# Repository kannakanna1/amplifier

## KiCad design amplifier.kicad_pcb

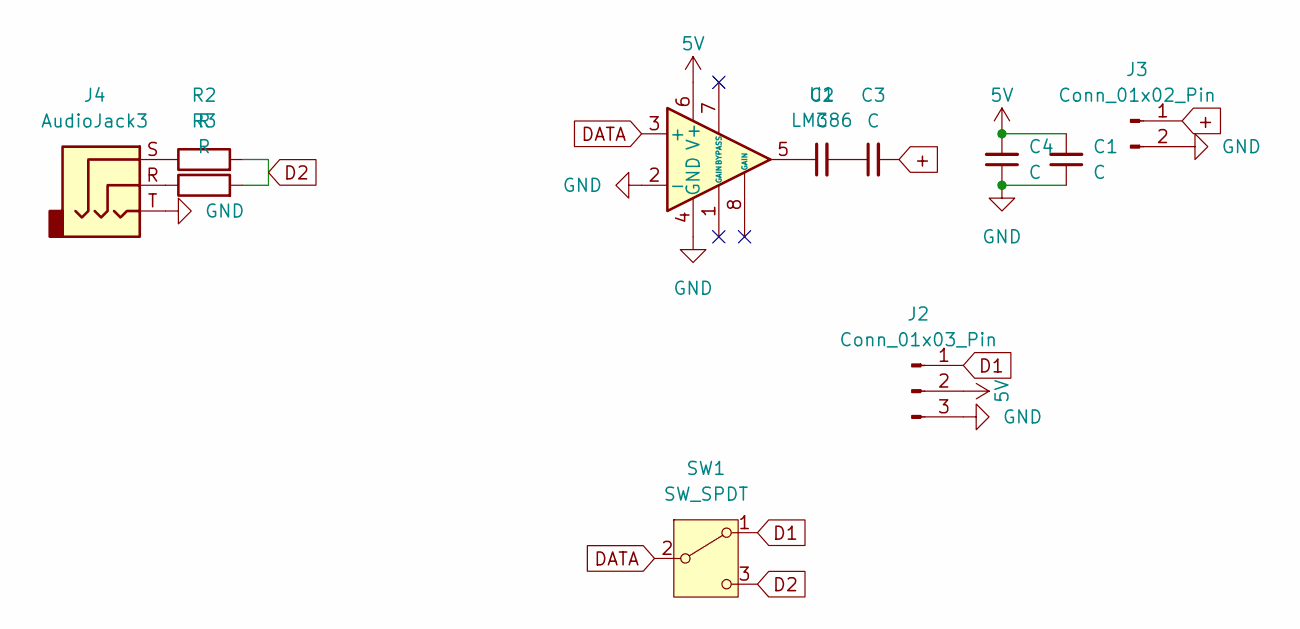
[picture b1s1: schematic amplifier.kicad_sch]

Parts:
C1, C2, C3, C4: C; C_1206_3216Metric
J2: Conn_01x03_Pin; PinHeader_1x03_P2.54mm_Vertical
J3: Conn_01x02_Pin; PinHeader_1x02_P2.54mm_Vertical
J4: AudioJack3; Jack_3.5mm_Switronic_ST-005-G_horizontal
R2, R3: R; R_0603_1608Metric
SW1: SW_SPDT; SW_Slide_SPDT_Straight_CK_OS102011MS2Q
U1: LM386; DIP-8_W7.62mm

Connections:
5V: C1.2, C4.2, J2.2, U1.6 (V+)
+: C3.2, J3.1
D1: J2.1, SW1.1 (A)
D2: R2.2, R3.2, SW1.3 (C)
DATA: SW1.2 (B), U1.3 (+)
GND: C1.1, C4.1, J2.3, J3.2, J4.T, U1.2 (-), U1.4 (GND)
unnamed: C2.1, U1.5
unnamed: C2.2, C3.1
unnamed: J4.R, R3.1
unnamed: J4.S, R2.1

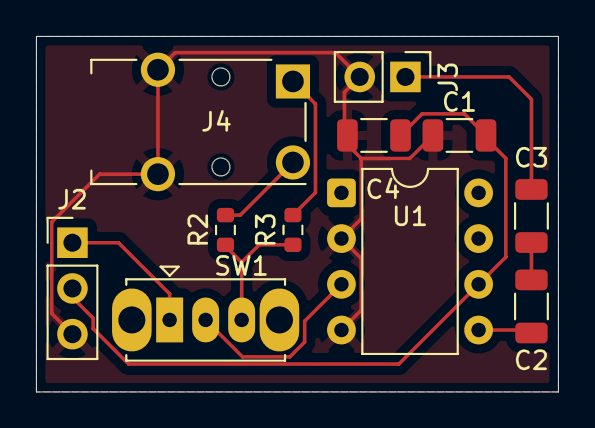
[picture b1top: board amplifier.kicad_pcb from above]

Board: 2 copper layers, 29.0 x 19.8 mm, 11 parts (0 on the bottom side), 10 nets.
